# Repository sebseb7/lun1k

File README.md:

lun1k
=====

find a toolchain here: https://launchpad.net/gcc-arm-embedded

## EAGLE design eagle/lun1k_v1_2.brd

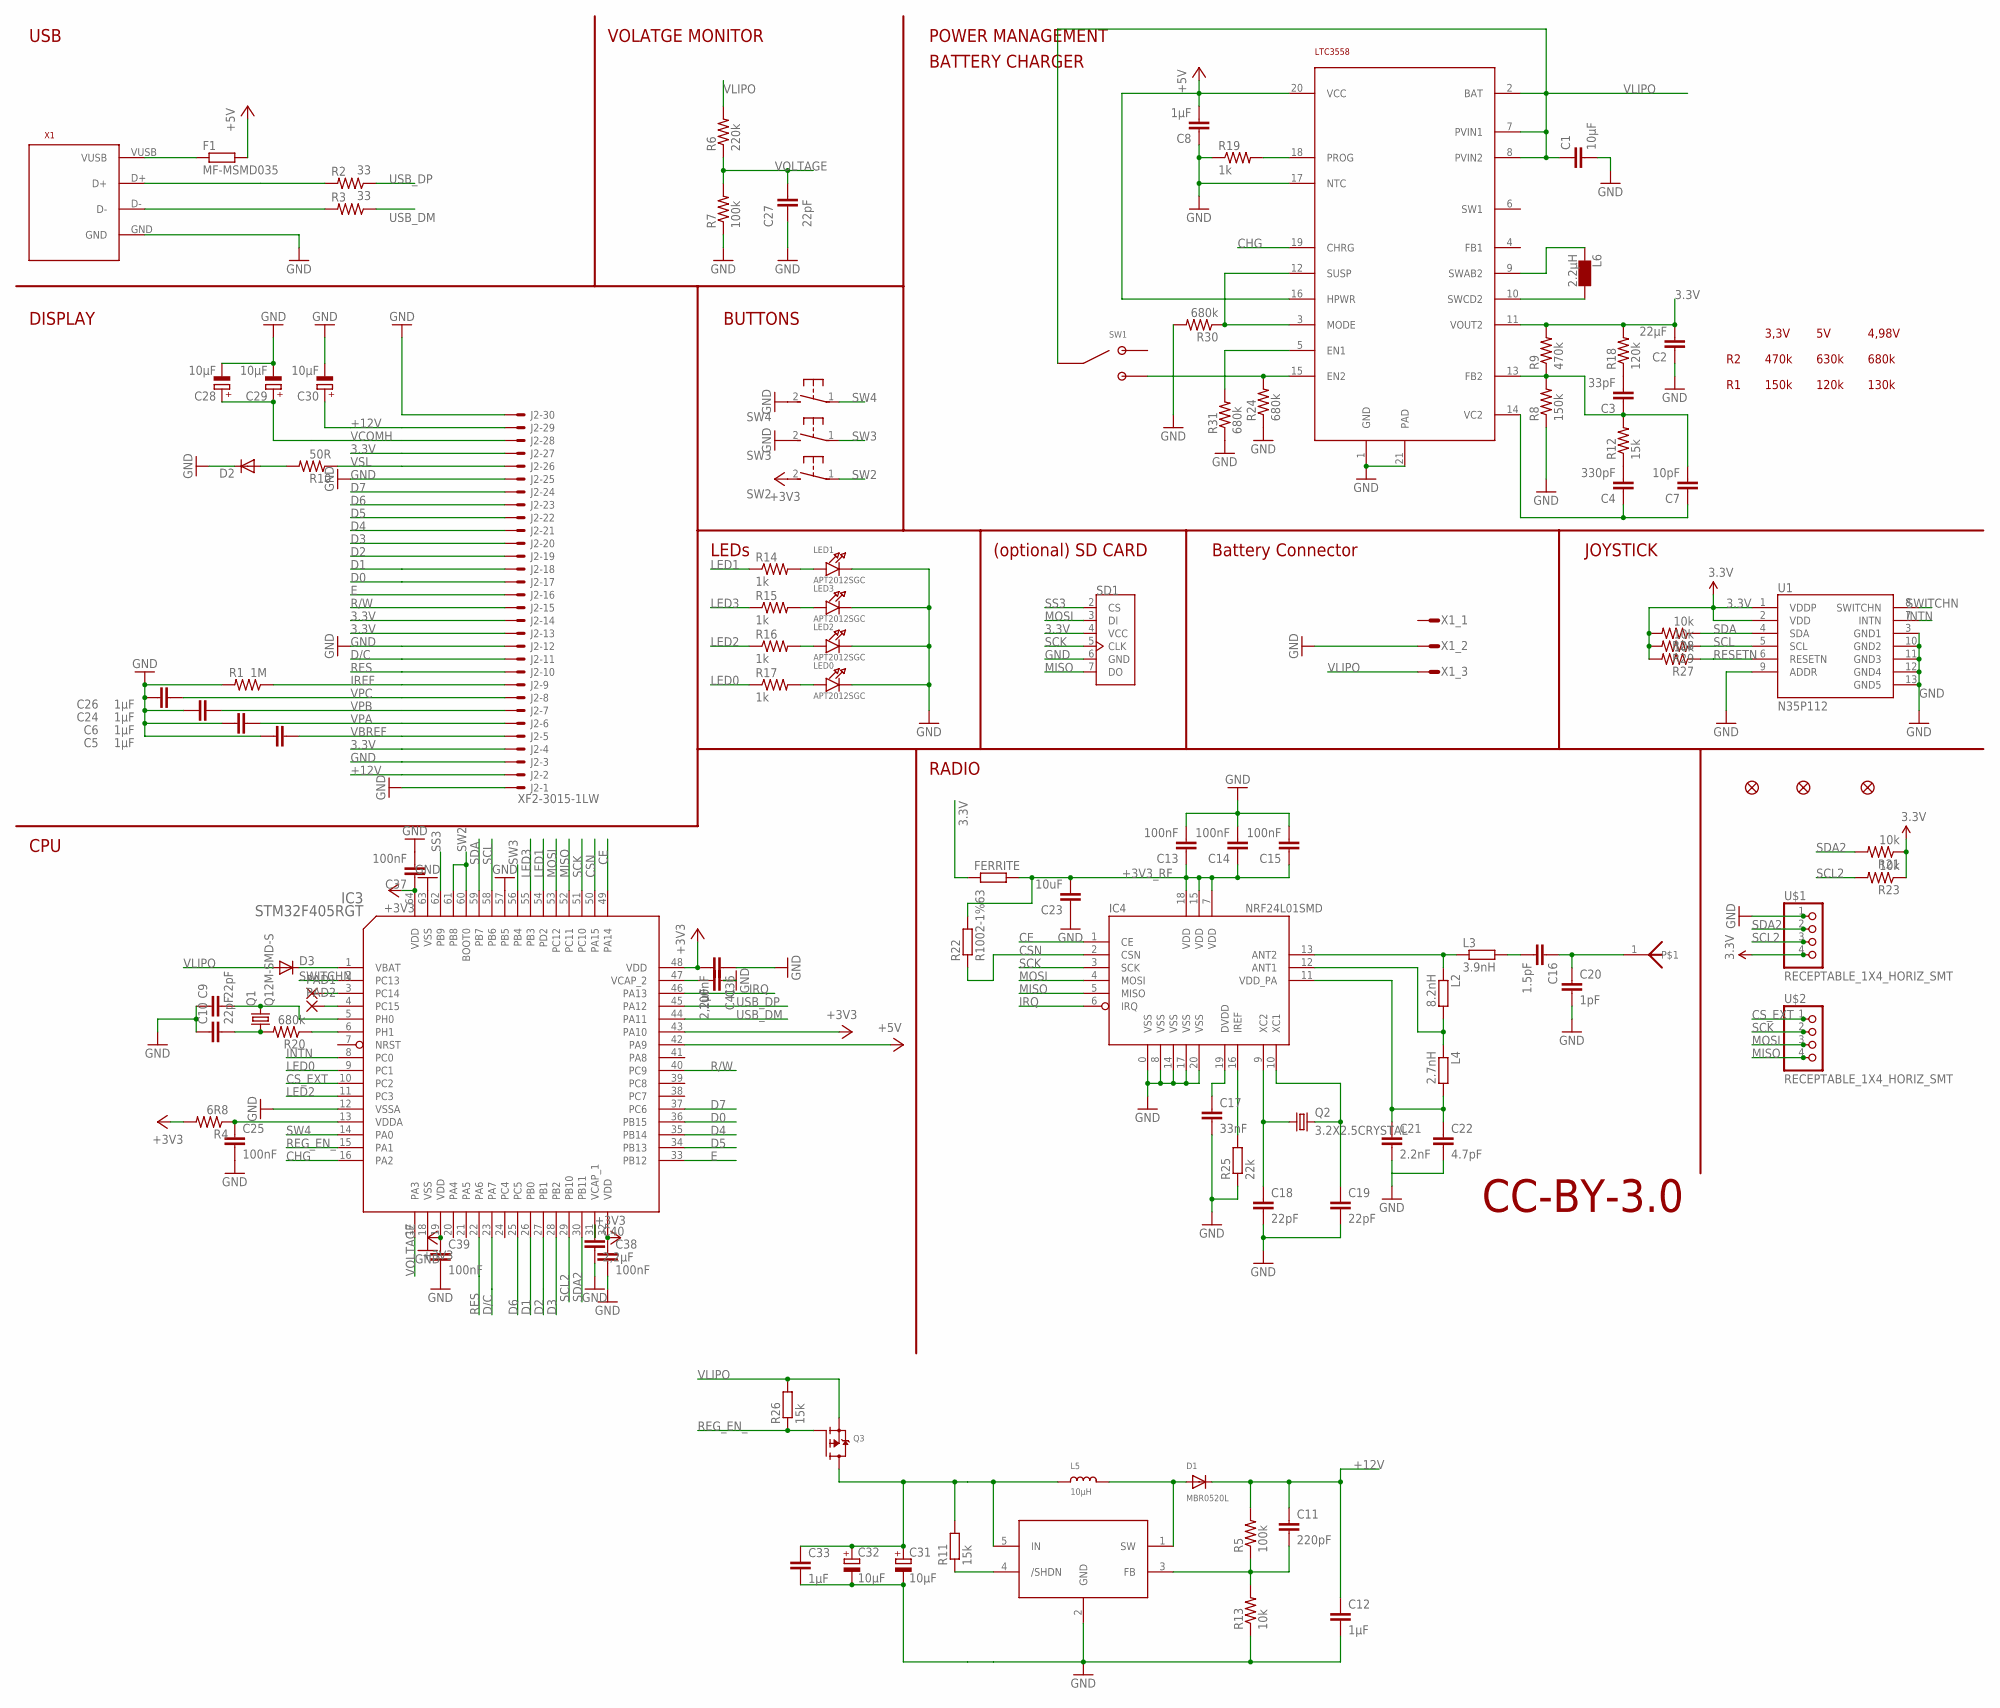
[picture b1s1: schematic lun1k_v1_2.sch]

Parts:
ANT: CHIPANTENNA
C1: 10µF; 0805
C2: 22µF; 0805
C3: 33pF; 0805
C4: 330pF; 0805
C5, C6, C8, C12, C24, C26, C33: 1µF; 0805
C7: 10pF; 0805
C9, C10, C27: 22pF; 0402-CAP
C11: 220pF; 0805
C13, C14, C15: 100nF; C0402K
C16: 1.5pF; C0402K
C17: 33nF; C0402K
C18, C19: 22pF; C0402K
C20: 1pF; C0402K
C21: 2.2nF; C0402K
C22: 4.7pF; C0402K
C23: 10uF; C0805K
C25, C36, C37, C38, C39: 100nF; 0402-CAP
C28, C29, C30, C31, C32: 10µF; SMC_A
C40, C41: 2,2µF; 0805
D1: MBR0520L; SOD-123
D2, D3: DIODE-SOD323-R; SOD323-R
F1: MF-MSMD035; R1210
FERRITE: R-EU_R0805; R0805
FID1, FID2, FID3: FIDUCIAL1.5X3; FIDUCIAL-1.5X3
IC1: LTC3558; UD-QFN20
IC2: LM27313; SOT23-5L
IC3: STM32F405RGT; LQFP64
IC4: NRF24L01SMD; QFN20
J2: XF2-3015-1LW; XF2H-3015-1LW
L2: 8.2nH; R0402
L3: 3.9nH; R0402
L4: 2.7nH; R0402
L5: 10µH; INDUCTOR_1007
L6: 2.2µH; CDRH3D16
LED0, LED1, LED2, LED3: APT2012SGC; CHIPLED_0805
PAD1, PAD2: SMD2; SMD1,27-2,54
Q1: Q12M-SMD-S; X22
Q2: 3.2X2.5CRYSTAL; CRYSTAL3.2X2.5
Q3: MOSFET-P; SOT23-R
R1: 1M; 0805
R2, R3: 33; 0402-RES
R4: 6R8; 0402-RES
R5: 100k; 0805
R6: 220k; 0402-RES
R7: 100k; 0402-RES
R8: 150k; 0805
R9: 470k; 0805
R10: 50R; 0805
R11, R26: 15k; R0402
R12: 15k; 0805
R13: 10k; 0805
R14, R15, R16, R17: 1k; 0402-RES
R18: 120k; 0805
R19: 1k; 0805
R20, R24, R30, R31: 680k; 0402-RES
R21, R23, R27, R28, R29: 10k; 0402-RES
R22: R1002-1%63; R0603
R25: 22k; R0603
SD1: MICROSD_SF-MICROSD; MICROSD_MICROSD
SW1: JS102011SAQN
SW2, SW3, SW4: SWITCH_MCTAEF
U1: N35P112
U$1, U$2: RECEPTABLE_1X4_HORIZ_SMT
X1: MICROUSB; MICROAB
X1_: JST-PH3

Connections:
3.3V: C2.2, C36.2, C37.1, C38.1, C39.1, FERRITE.1, IC1.11 (VOUT2), IC3.19 (VDD), IC3.32 (VDD), IC3.43 (PA10), IC3.48 (VDD), IC3.64 (VDD), J2.4 (MS), J2.13 (MS), J2.14 (MS), J2.27 (MS), R4.2, R9.2, R18.2, R21.1, R23.1, R27.2, R28.2, R29.2, SD1.4 (VCC), SW2.2, U1.1 (VDDP), U1.2 (VDD), U$1.4, U$1.4@1 (4)
+3V3_RF: C13.1, C14.1, C15.1, C23.2, FERRITE.2, IC4.7 (VDD), IC4.15 (VDD), IC4.18 (VDD), R22.2
+5V: C8.2, F1.2, IC1.16 (HPWR), IC1.20 (VCC), IC3.42 (PA9)
+12V: C11.1, C12.1, C30.+, D1.C, J2.2 (MS), J2.29 (MS), R5.2
CE: IC3.49 (PA14), IC4.1 (CE)
CHG: IC1.19 (CHRG), IC3.16 (PA2)
CSN: IC3.50 (PA15), IC4.2 (CSN), R22.1
CS_EXT: IC3.10 (PC2), U$2.1, U$2.1@1 (1)
D0: IC3.36 (PB15), J2.17 (MS)
D1: IC3.26 (PB0), J2.18 (MS)
D2: IC3.27 (PB1), J2.19 (MS)
D3: IC3.28 (PB2), J2.20 (MS)
D4: IC3.35 (PB14), J2.21 (MS)
D5: IC3.34 (PB13), J2.22 (MS)
D6: IC3.25 (PC5), J2.23 (MS)
D7: IC3.37 (PC6), J2.24 (MS)
D+: R2.2, X1.D+
D-: R3.2, X1.D-
D/C: IC3.23 (PA7), J2.11 (MS)
E: IC3.33 (PB12), J2.16 (MS)
EN2: IC1.15 (EN2), R24.2, SW1.3
GND: C1.2, C2.1, C5.1, C6.1, C8.1, C9.1, C10.1, C12.2, C13.2, C14.2, C15.2, C17.2, C18.2, C19.2, C20.2, C21.2, C22.2, C23.1, C24.1, C25.2, C26.1, C27.1, C28.-, C29.-, C30.-, C31.-, C32.-, C33.2, C36.1, C37.2, C38.2, C39.2, C40.2, C41.1, D2.C, IC1.1 (GND), IC1.17 (NTC), IC1.21 (PAD), IC2.2 (GND), IC3.12 (VSSA), IC3.18 (VSS), IC3.57 (PB5), IC3.63 (VSS), IC4.0 (VSS), IC4.8 (VSS), IC4.14 (VSS), IC4.17 (VSS), IC4.20 (VSS), J2.1 (MSV), J2.3 (MS), J2.12 (MS), J2.25 (MS), J2.30 (MS), LED0.C, LED1.C, LED2.C, LED3.C, R1.2, R7.1, R8.1, R13.1, R19.1, R24.1, R25.1, R30.2, R31.1, SD1.6 (GND), SW3.2, SW4.2, U1.3 (GND1), U1.9 (ADDR), U1.10 (GND2), U1.11 (GND3), U1.12 (GND4), U1.13 (GND5), U$1.1, U$1.1@1 (1), X1.GND, X1_.2
INTN: IC3.8 (PC0), U1.7 (INTN)
IREF: J2.9 (MS), R1.1
IRQ: IC3.46 (PA13), IC4.6 (IRQ)
LED0: IC3.9 (PC1), R17.1
LED1: IC3.54 (PD2), R14.1
LED2: IC3.11 (PC3), R16.1
LED3: IC3.55 (PB3), R15.1
MISO: IC3.52 (PC11), IC4.5 (MISO), SD1.7 (DO), U$2.4, U$2.4@1 (4)
MOSI: IC3.53 (PC12), IC4.4 (MOSI), SD1.3 (DI), U$2.3, U$2.3@1 (3)
unnamed: C9.2, IC3.5 (PH0), Q1.3 (2)
unnamed: IC1.18 (PROG), R19.2
unnamed: C10.2, Q1.1, R20.2
unnamed: LED0.A, R17.2
unnamed: LED2.A, R16.2
unnamed: LED3.A, R15.2
unnamed: C3.1, C7.2, IC1.13 (FB2), R8.2, R9.1, R12.2
unnamed: F1.1, X1.VUSB
unnamed: LED1.A, R14.2
unnamed: C18.1, IC4.9 (XC2), Q2.1
unnamed: C19.1, IC4.10 (XC1), Q2.3 (2)
unnamed: ANT.1, C16.1, C20.1
unnamed: C3.2, R18.1
unnamed: D2.A, R10.2
unnamed: C25.1, IC3.13 (VDDA), R4.1
unnamed: C4.2, R12.1
unnamed: C4.1, C7.1, IC1.14 (VC2)
unnamed: IC1.10 (SWCD2), L6.P$1 (1)
unnamed: C40.1, IC3.31 (VCAP_1)
unnamed: C41.2, IC3.47 (VCAP_2)
unnamed: IC3.3 (PC14), PAD1.1
unnamed: IC1.9 (SWAB2), L6.P$2 (2)
unnamed: IC3.4 (PC15), PAD2.1
unnamed: D1.A, IC2.1 (SW), L5.P$2 (2)
unnamed: IC1.3 (MODE), IC1.12 (SUSP), R30.1
unnamed: C11.2, IC2.3 (FB), R5.1, R13.2
unnamed: IC1.5 (EN1), R31.2
unnamed: IC3.6 (PH1), R20.1
unnamed: D3.C, IC3.1 (VBAT)
unnamed: IC2.4 (/SHDN), R11.1
unnamed: C17.1, IC4.19 (DVDD)
unnamed: IC4.16 (IREF), R25.2
unnamed: C21.1, C22.1, IC4.11 (VDD_PA), L4.2
unnamed: IC4.12 (ANT1), L2.2, L4.1
unnamed: IC4.13 (ANT2), L2.1, L3.1
unnamed: C16.2, L3.2
R/W: IC3.40 (PC9), J2.15 (MS)
REG_EN_: IC3.15 (PA1), Q3.1 (G), R26.1
RES: IC3.22 (PA6), J2.10 (MS)
RESETN: R27.1, U1.6 (RESETN)
SCK: IC3.51 (PC10), IC4.3 (SCK), SD1.5 (CLK), U$2.2, U$2.2@1 (2)
SCL: IC3.58 (PB6), R29.1, U1.5 (SCL)
SCL2: IC3.29 (PB10), R23.2, U$1.3, U$1.3@1 (3)
SDA: IC3.59 (PB7), R28.1, U1.4 (SDA)
SDA2: IC3.30 (PB11), R21.2, U$1.2, U$1.2@1 (2)
SS3: IC3.62 (PB9), SD1.2 (CS)
SW2: IC3.60 (BOOT0), IC3.61 (PB8), SW2.1
SW3: IC3.56 (PB4), SW3.1
SW4: IC3.14 (PA0), SW4.1
SWITCHN: IC3.2 (PC13), U1.8 (SWITCHN)
USB_DM: IC3.44 (PA11), R3.1
USB_DP: IC3.45 (PA12), R2.1
VBREF: C5.2, J2.5 (MS)
VCOMH: C28.+, C29.+, J2.28 (MS)
VLIPO: C1.1, D3.A, IC1.2 (BAT), IC1.7 (PVIN1), IC1.8 (PVIN2), Q3.2 (S), R6.2, R26.2, SW1.2, X1_.3
VOLTAGE: C27.2, IC3.17 (PA3), R6.1, R7.2
VPA: C6.2, J2.6 (MS)
VPB: C24.2, J2.7 (MS)
VPC: C26.2, J2.8 (MS)
VREGIN: C31.+, C32.+, C33.1, IC2.5 (IN), L5.P$1 (1), Q3.3 (D), R11.2
VSL: J2.26 (MS), R10.1

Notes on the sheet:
POWER MANAGEMENT
DISPLAY
USB
BATTERY CHARGER
VOLATGE MONITOR
LEDs
(optional) SD CARD
JOYSTICK
CPU
RADIO
CC-BY-3.0
BUTTONS
3,3V
4,98V
470k
150k
630k
120k
680k
130k
Battery Connector

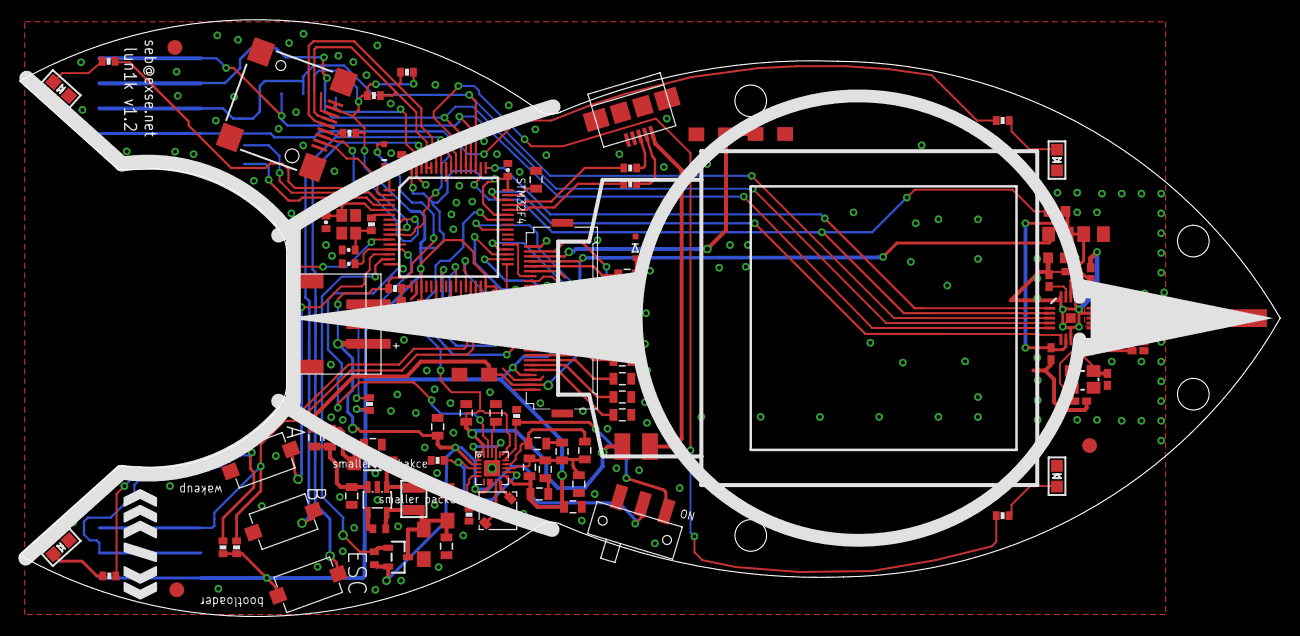
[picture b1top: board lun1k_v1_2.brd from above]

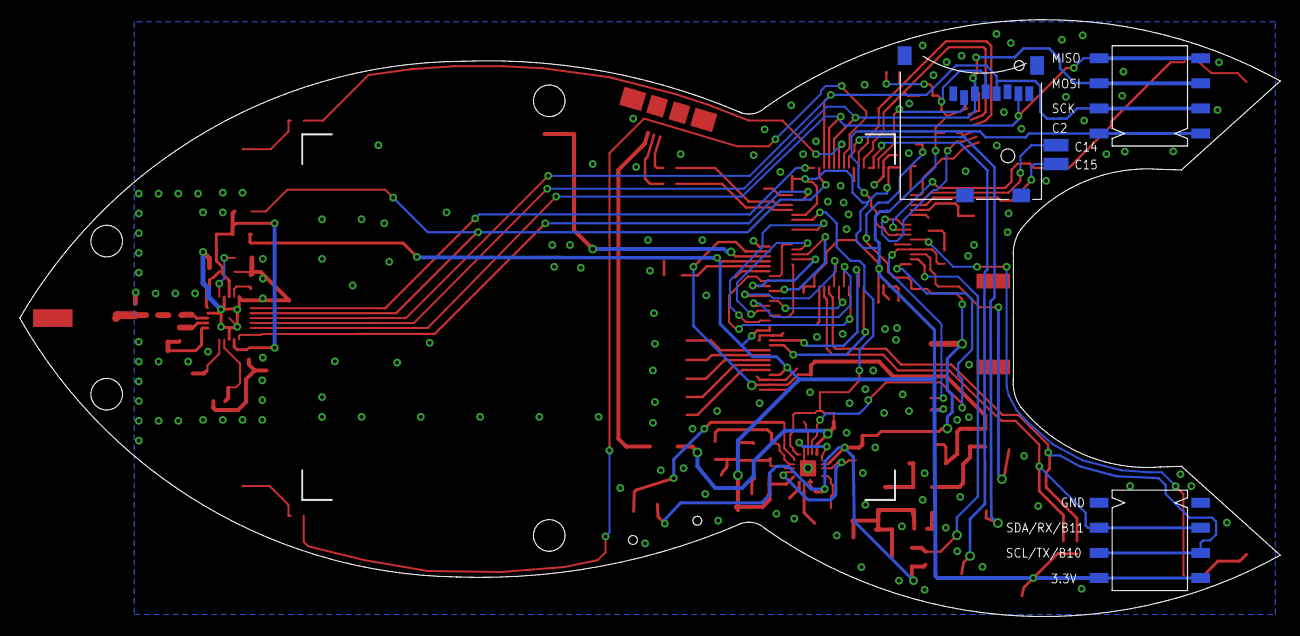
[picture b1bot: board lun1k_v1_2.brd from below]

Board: 2 copper layers, 127.6 x 60.4 mm, 108 parts (5 on the bottom side), 92 nets.

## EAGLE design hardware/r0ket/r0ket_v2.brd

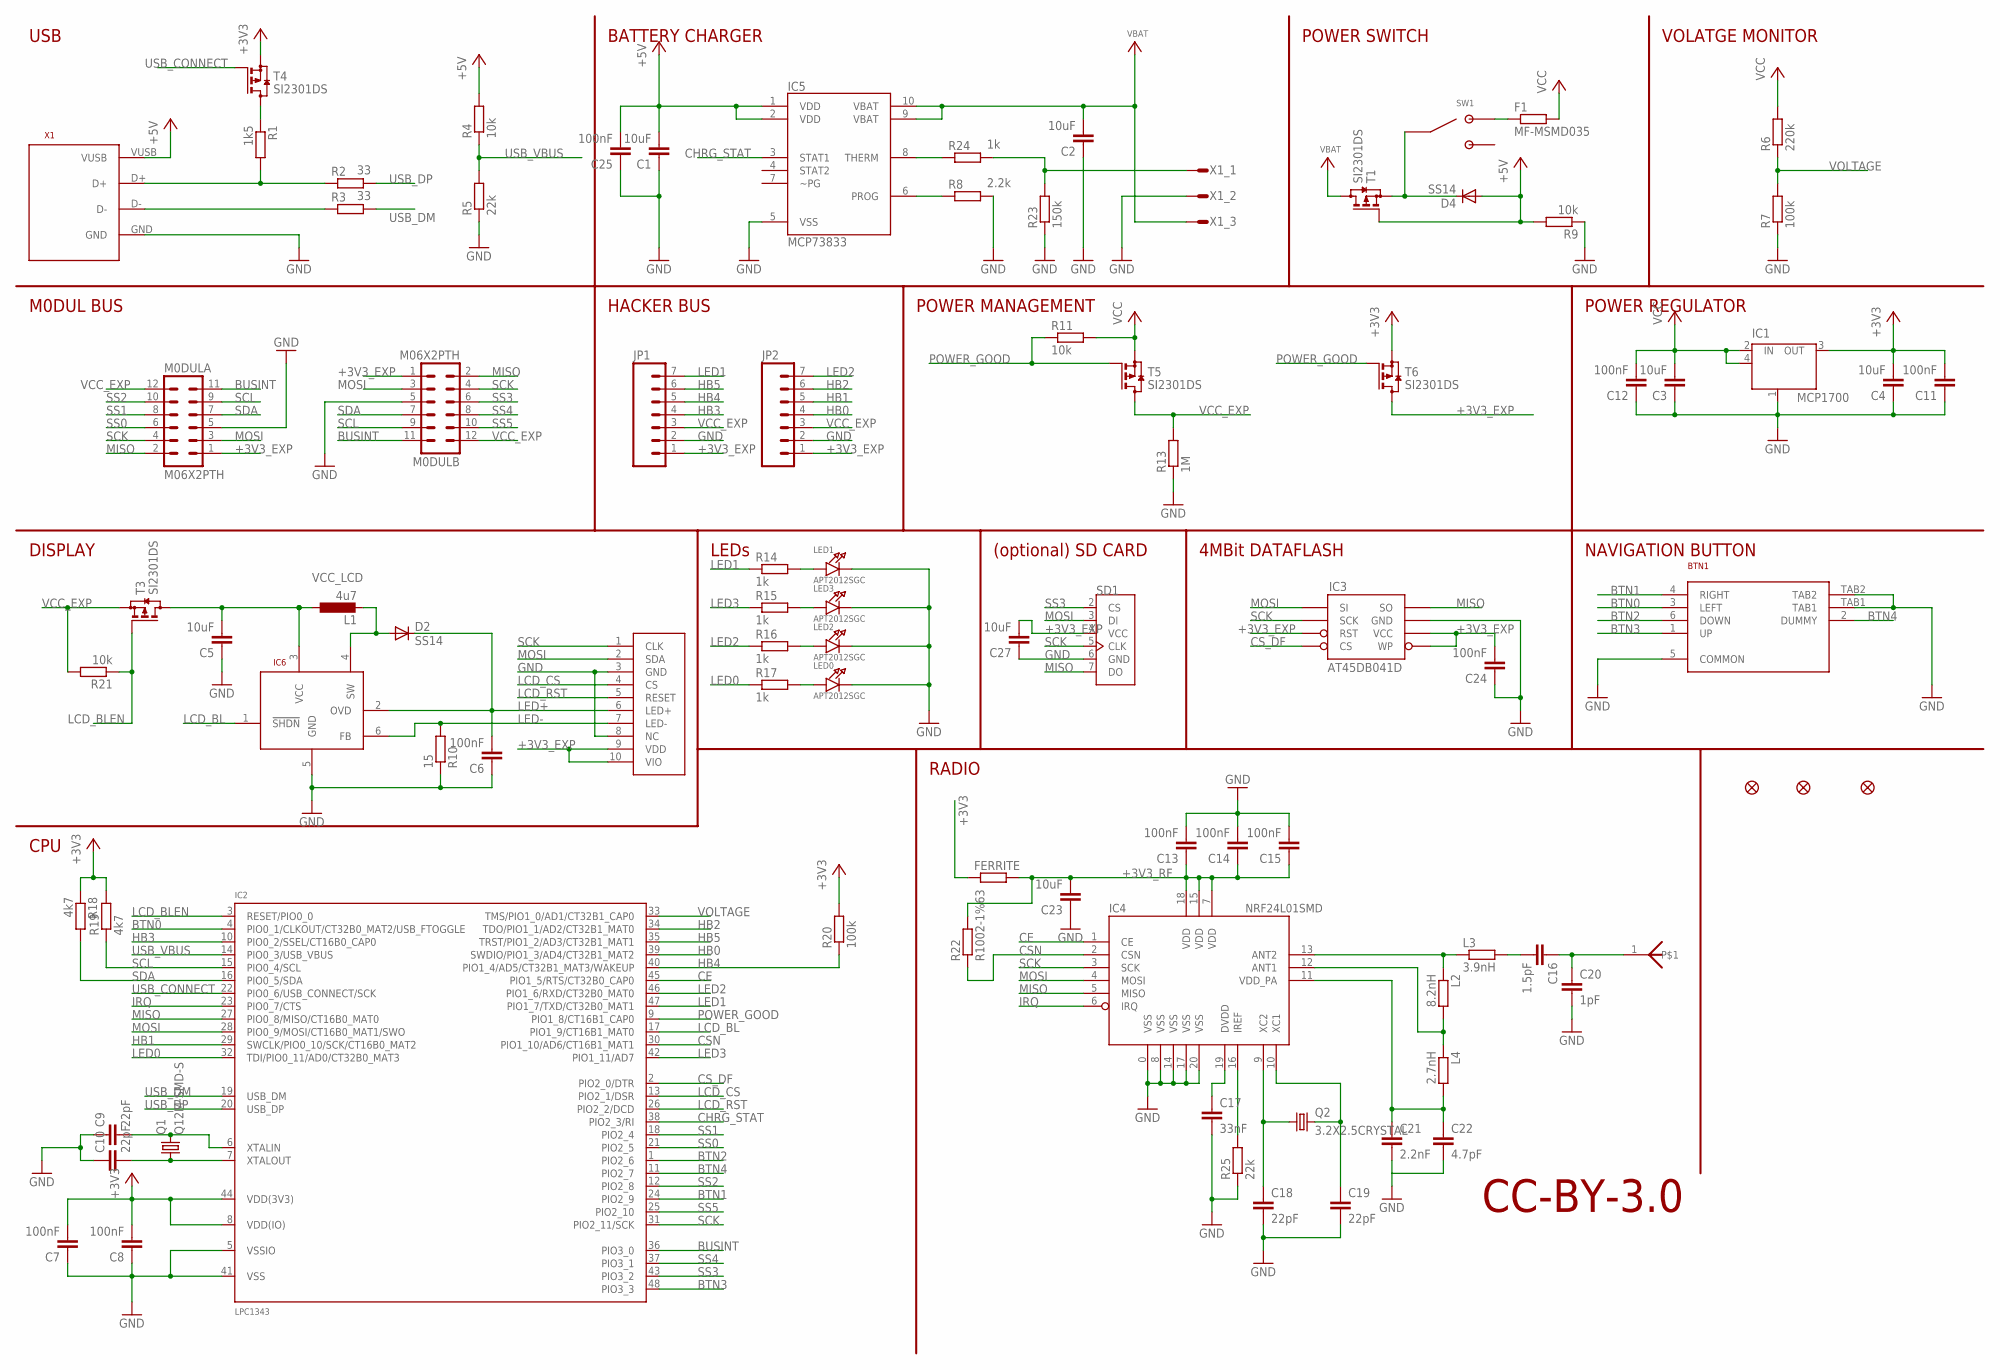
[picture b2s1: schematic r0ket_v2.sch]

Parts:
ANT: CHIPANTENNA
BTN1: MCMT5-F-V
C1, C2, C3, C4, C5, C23, C27: 10uF; C0805K
C6, C7, C8, C11, C12, C13, C14, C15, C24, C25: 100nF; C0402K
C9, C10, C18, C19: 22pF; C0402K
C16: 1.5pF; C0402K
C17: 33nF; C0402K
C20: 1pF; C0402K
C21: 2.2nF; C0402K
C22: 4.7pF; C0402K
D2, D4: SS14; SMB
F1: MF-MSMD035; R1210
FERRITE: R-EU_R0805; R0805
FID1, FID2, FID3: FIDUCIAL1.5X3; FIDUCIAL-1.5X3
IC1: MCP1700; SOT89
IC2: LPC1343; LQFP48
IC3: AT45DB041D; SO08
IC4: NRF24L01SMD; QFN20
IC5: MCP73833; MSOP-10
IC6: TB62737; SUPERSOT6
JP1, JP2: M07; 1X07
L1: 4u7; 0806
L2: 8.2nH; R0402
L3: 3.9nH; R0402
L4: 2.7nH; R0402
LED0, LED1, LED2, LED3: APT2012SGC; CHIPLED_0805
M0DULA, M0DULB: M06X2PTH; MA06-2
Q1: Q12M-SMD-S; CTS406
Q2: 3.2X2.5CRYSTAL; CRYSTAL3.2X2.5
R1: 1k5; R0603
R2, R3: 33; R0603
R4, R9, R11, R21: 10k; R0603
R5, R25: 22k; R0603
R6: 220k; R0603
R7, R20: 100k; R0603
R8: 2.2k; R0603
R10: 15; R0603
R13: 1M; R0603
R14, R15, R16, R17, R24: 1k; R0603
R18, R19: 4k7; R0603
R22: R1002-1%63; R0603
R23: 150k; R0603
SD1: MICROSD_SF-MICROSD; MICROSD_MICROSD
SW1: JS102011SAQN
T1, T3, T4, T5, T6: SI2301DS; SOT23
X1: MICROUSB; MICROAB
X1_: JST-PH3
X2: NOKIA; DF23

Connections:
+3V3: C4.2, C7.2, C8.2, C11.2, FERRITE.1, IC1.3 (OUT), IC2.8 (VDD(IO)), IC2.44 (VDD(3V3)), R18.1, R19.2, R20.2, T4.2 (S), T6.2 (S)
+3V3_EXP: C24.2, C27.2, IC3.3 (RST), IC3.5 (WP), IC3.6 (VCC), JP1.1, JP2.1, M0DULA.1, M0DULB.1, SD1.4 (VCC), T6.3 (D), X2.9 (VDD), X2.10 (VIO)
+3V3_RF: C13.1, C14.1, C15.1, C23.2, FERRITE.2, IC4.7 (VDD), IC4.15 (VDD), IC4.18 (VDD), R22.2
+5V: C1.2, C25.2, D4.A, IC5.1 (VDD), IC5.2 (VDD), R4.2, R9.2, T1.1 (G), X1.VUSB
BTN0: BTN1.3 (LEFT), IC2.4 (PIO0_1/CLKOUT/CT32B0_MAT2/USB_FTOGGLE)
BTN1: BTN1.4 (RIGHT), IC2.24 (PIO2_9)
BTN2: BTN1.6 (DOWN), IC2.1 (PIO2_6)
BTN3: BTN1.1 (UP), IC2.48 (PIO3_3)
BTN4: BTN1.2 (DUMMY), IC2.11 (PIO2_7)
BUSINT: IC2.36 (PIO3_0), M0DULA.11, M0DULB.11
CE: IC2.45 (PIO1_5/RTS/CT32B0_CAP0), IC4.1 (CE)
CHRG_STAT: IC2.38 (PIO2_3/RI), IC5.3 (STAT1)
CSN: IC2.30 (PIO1_10/AD6/CT16B1_MAT1), IC4.2 (CSN), R22.1
CS_DF: IC2.2 (PIO2_0/DTR), IC3.4 (CS)
D+: R1.2, R2.2, X1.D+
D-: R3.2, X1.D-
GND: BTN1.5 (COMMON), BTN1.TAB1, BTN1.TAB2, C1.1, C2.1, C3.1, C4.1, C5.1, C6.1, C7.1, C8.1, C9.1, C10.1, C11.1, C12.1, C13.2, C14.2, C15.2, C17.2, C18.2, C19.2, C20.2, C21.2, C22.2, C23.1, C24.1, C25.1, C27.1, IC1.1 (GND/ADJ), IC2.5 (VSSIO), IC2.41 (VSS), IC3.7 (GND), IC4.0 (VSS), IC4.8 (VSS), IC4.14 (VSS), IC4.17 (VSS), IC4.20 (VSS), IC5.5 (VSS), IC6.5 (GND), JP1.2, JP2.2, LED0.C, LED1.C, LED2.C, LED3.C, M0DULA.5, M0DULB.5, R5.1, R7.1, R8.1, R9.1, R10.1, R13.1, R23.1, R25.1, SD1.6 (GND), X1.GND, X1_.2, X2.3 (GND), X2.8 (NC)
HB0: IC2.39 (SWDIO/PIO1_3/AD4/CT32B1_MAT2), JP2.4
HB1: IC2.29 (SWCLK/PIO0_10/SCK/CT16B0_MAT2), JP2.5
HB2: IC2.34 (TDO/PIO1_1/AD2/CT32B1_MAT0), JP2.6
HB3: IC2.10 (PIO0_2/SSEL/CT16B0_CAP0), JP1.4
HB4: IC2.40 (PIO1_4/AD5/CT32B1_MAT3/WAKEUP), JP1.5, R20.1
HB5: IC2.35 (TRST/PIO1_2/AD3/CT32B1_MAT1), JP1.6
IRQ: IC2.23 (PIO0_7/CTS), IC4.6 (IRQ)
LCD_BL: IC2.17 (PIO1_9/CT16B1_MAT0), IC6.1 (!SHDN)
LCD_BLEN: IC2.3 (RESET/PIO0_0), R21.1, T3.1 (G)
LCD_CS: IC2.13 (PIO2_1/DSR), X2.4 (CS)
LCD_RST: IC2.26 (PIO2_2/DCD), X2.5 (RESET)
LED0: IC2.32 (TDI/PIO0_11/AD0/CT32B0_MAT3), R17.1
LED1: IC2.47 (PIO1_7/TXD/CT32B0_MAT1), JP1.7, R14.1
LED2: IC2.46 (PIO1_6/RXD/CT32B0_MAT0), JP2.7, R16.1
LED3: IC2.42 (PIO1_11/AD7), R15.1
LED+: C6.2, D2.C, IC6.2 (OVD), X2.6 (LED+)
LED-: IC6.6 (FB), R10.2, X2.7 (LED-)
MISO: IC2.27 (PIO0_8/MISO/CT16B0_MAT0), IC3.8 (SO), IC4.5 (MISO), M0DULA.2, M0DULB.2, SD1.7 (DO)
MOSI: IC2.28 (PIO0_9/MOSI/CT16B0_MAT1/SWO), IC3.1 (SI), IC4.4 (MOSI), M0DULA.3, M0DULB.3, SD1.3 (DI), X2.2 (SDA)
unnamed: C9.2, IC2.6 (XTALIN), Q1.3 (2)
unnamed: IC5.8 (THERM), R24.2
unnamed: C10.2, IC2.7 (XTALOUT), Q1.1
unnamed: LED0.A, R17.2
unnamed: LED2.A, R16.2
unnamed: LED3.A, R15.2
unnamed: R23.2, R24.1, X1_.1
unnamed: D4.C, SW1.2, T1.2 (S)
unnamed: LED1.A, R14.2
unnamed: C18.1, IC4.9 (XC2), Q2.1
unnamed: C19.1, IC4.10 (XC1), Q2.3 (2)
unnamed: ANT.1, C16.1, C20.1
unnamed: IC5.6 (PROG), R8.2
unnamed: D2.A, IC6.4 (SW), L1.2
unnamed: F1.1, SW1.1
unnamed: R1.1, T4.3 (D)
unnamed: C17.1, IC4.19 (DVDD)
unnamed: IC4.16 (IREF), R25.2
unnamed: C21.1, C22.1, IC4.11 (VDD_PA), L4.2
unnamed: IC4.12 (ANT1), L2.2, L4.1
unnamed: IC4.13 (ANT2), L2.1, L3.1
unnamed: C16.2, L3.2
POWER_GOOD: IC2.9 (PIO1_8/CT16B1_CAP0), R11.1, T5.1 (G), T6.1 (G)
SCK: IC2.31 (PIO2_11/SCK), IC3.2 (SCK), IC4.3 (SCK), M0DULA.4, M0DULB.4, SD1.5 (CLK), X2.1 (CLK)
SCL: IC2.15 (PIO0_4/SCL), M0DULA.9, M0DULB.9, R19.1
SDA: IC2.16 (PIO0_5/SDA), M0DULA.7, M0DULB.7, R18.2
SS0: IC2.21 (PIO2_5), M0DULA.6
SS1: IC2.18 (PIO2_4), M0DULA.8
SS2: IC2.12 (PIO2_8), M0DULA.10
SS3: IC2.43 (PIO3_2), M0DULB.6, SD1.2 (CS)
SS4: IC2.37 (PIO3_1), M0DULB.8
SS5: IC2.25 (PIO2_10), M0DULB.10
USB_CONNECT: IC2.22 (PIO0_6/USB_CONNECT/SCK), T4.1 (G)
USB_DM: IC2.19 (USB_DM), R3.1
USB_DP: IC2.20 (USB_DP), R2.1
USB_VBUS: IC2.14 (PIO0_3/USB_VBUS), R4.1, R5.2
VBAT: C2.2, IC5.9 (VBAT), IC5.10 (VBAT), T1.3 (D), X1_.3
VCC: C3.2, C12.2, F1.2, IC1.2 (IN), IC1.4 (IN), R6.2, R11.2, T5.2 (S)
VCC_EXP: JP1.3, JP2.3, M0DULA.12, M0DULB.12, R13.2, R21.2, T3.2 (S), T5.3 (D)
VCC_LCD: C5.2, IC6.3 (VCC), L1.1, T3.3 (D)
VOLTAGE: IC2.33 (TMS/PIO1_0/AD1/CT32B1_CAP0), R6.1, R7.2

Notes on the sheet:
M0DUL BUS
HACKER BUS
POWER MANAGEMENT
POWER REGULATOR
DISPLAY
USB
BATTERY CHARGER
POWER SWITCH
VOLATGE MONITOR
LEDs
(optional) SD CARD
4MBit DATAFLASH
NAVIGATION BUTTON
CPU
RADIO
CC-BY-3.0

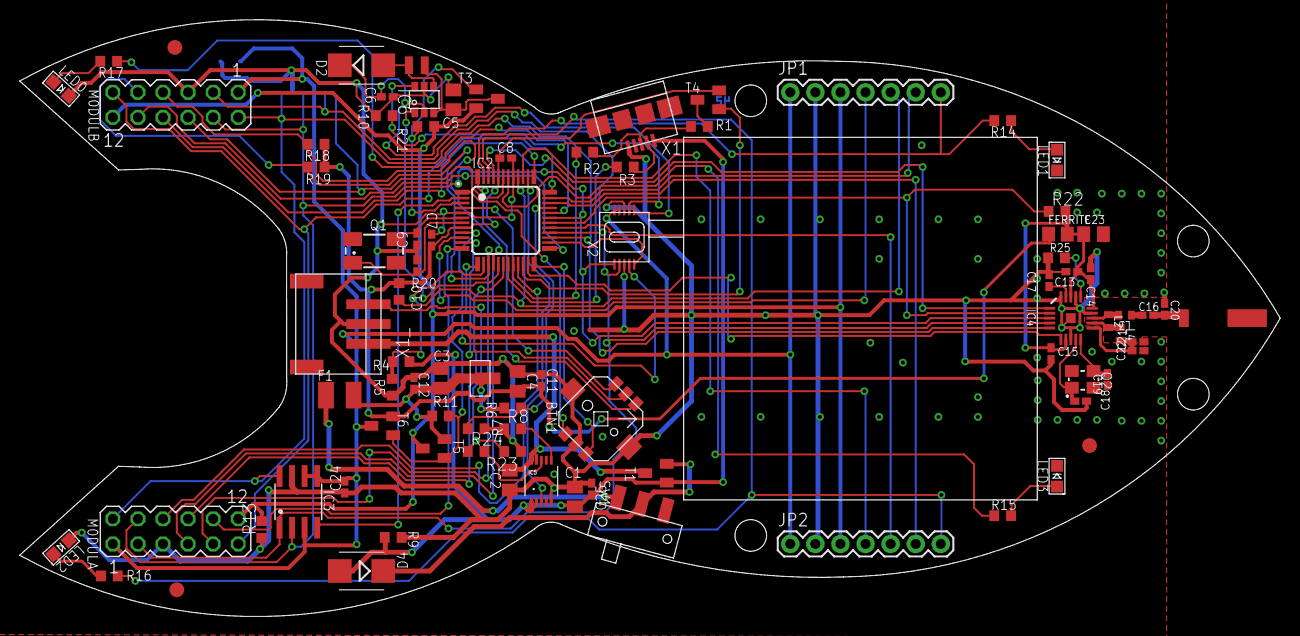
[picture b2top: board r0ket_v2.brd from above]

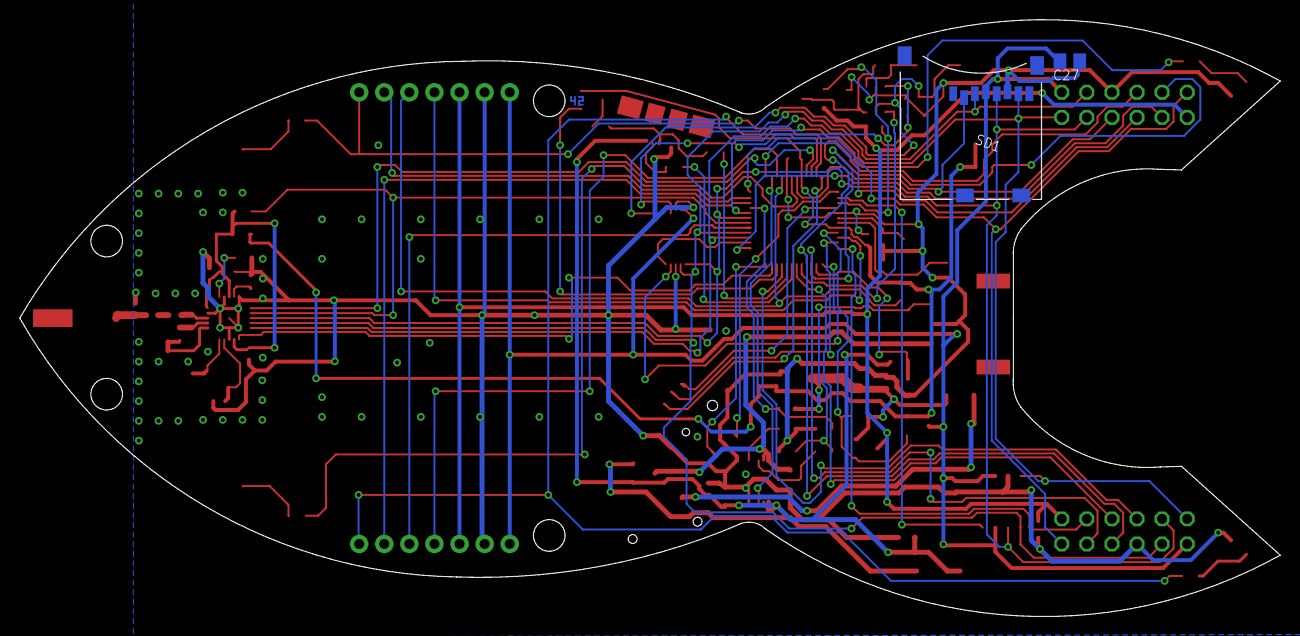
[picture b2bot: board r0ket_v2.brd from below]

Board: 2 copper layers, 127.6 x 60.4 mm, 89 parts (2 on the bottom side), 77 nets.

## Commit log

2012-09-26 removed everything except r0ket_v2.sch r0ket_v2.brd and badge.lbr
2012-09-26 converted all eagle files to v6
2012-09-26 removed a lot of components
2012-09-26 renamed eagle files
2012-09-27 added oled and 12v regulator
2012-09-27 added farnell number for pfc connector
2012-09-27 some wire cleanup
2012-09-27 added cpu
2012-09-27 fixed oled placement
2012-09-27 placed components for the oled
2012-09-27 placed mcu
2012-09-27 replaced 0402 packages
2012-09-27 smaller crystal
2012-09-27 routing
2012-09-27 placed analog joystick
2012-09-27 placed buttons
2012-09-27 completely removed old supply & management
2012-09-27 some resistors: 0603 -> 0402
2012-09-27 new lipo charger
2012-09-27 button text
2012-09-27 routeing
2012-09-27 current progress of the routing
2012-09-27 module connector
2012-10-01 labeling
2012-10-01 milestone 1
2012-10-01 initial sumulator
2012-10-01 api change
2012-10-01 added 8x6 font
2012-10-01 switch 12V supply part 1
2012-10-01 switch 12V supply part 2
2012-10-01 font-template
2012-10-01 regulator final
2012-10-01 second ani
2012-10-03 updated images
2012-10-04 new variable-width 21pt font added
2012-10-04 small fixes
2012-10-04 remove old font and new lunik image
2012-10-05 unfinifhsed drivers
2012-11-01 minor changes
2012-11-02 post production fixes
2012-11-02 merge
2012-11-07 sim/Makefile: add Linux FLAGS for SDL
2012-11-07 tunnel animation
2012-11-07 animations/tunnel: bricked texture attempt
2012-11-07 cleanup, fixed some compiler warnings, lun1k <-> simulator compatibility
2012-11-07 fix for clang warning
2012-11-07 renamed attribute for constructor
2012-11-07 cleanup and directory reorganisation
2012-11-07 all globals should be static
2012-11-07 only 8k instead of 184k
2012-11-07 typo
2012-11-07 reorganize repo
2012-11-07 gitignore
2012-11-07 new animation
2012-11-07 font tools
2012-11-07 initial version of lun1k firmware
2012-11-07 printf now from libc
2012-11-08 limit fps to 30
2012-11-08 animations/tunnel: textured
2012-11-08 animations/tunnel_less_ram: texture & shading likewise
2012-11-08 animations/tunnel_less_ram: subsampling
2012-11-08 cleanup
2012-11-08 sim: smarter FRAMETIME
2012-11-08 sim: fix font path on linux
2012-11-08 animations/tunnel_less_ram: fiddle parameters
2012-11-08 animations/tunnel_less_ram: fix subsampling
2012-11-08 only 6 bit colors, like lun1k
2012-11-08 made a few things const
2012-11-08 slower is more realistic
2012-11-08 moved
2012-11-08 cleanup and cunstructor support for stm32f2
2012-11-08 readded asserts
2012-11-09 added fill_8x6
2012-11-09 simple tetris demo with 3 bots
2012-11-10 texture for todays party
2012-11-14 better gamma correction
2012-11-14 button support, smaller changes
2012-11-14 fixes
2012-11-14 color and button stub
2012-11-14 changed animationset
2012-11-14 no fsaa and no textture tunnel
2012-11-14 remoted 2nd texture
2012-11-14 removed F2 support
2012-11-14 added link to working stm32f4 toolchain
2012-11-14 fix math.c for simulator
2012-11-14 removed sdl_ttf dpendency
2012-11-14 animations: beginnings of a silly jumpnrun
2012-11-14 import fgl
    http://fgl.googlecode.com/svn/trunk/ at r17
2012-11-14 import libfixmath
    http://libfixmath.googlecode.com/svn/trunk/ at r84
2012-11-15 fgl_cube works in the sim
2012-11-15 fgl_cube: texture
2012-11-15 attempt to bring fgl to firmware
2012-11-16 tunnel
2012-11-17 debounce for all 4 buttons
2012-11-18 removed old tunnel
2012-11-18 removed 4xfsaa
2012-11-18 renamed tunnel_less_ram -> tunnel
2012-11-18 renamed tunnel_noaa -> tunnel_no_tex
2012-11-18 key support
2012-11-18 only stick key skips
2012-11-18 removed fgl (was included by accident)
2012-11-18 missing merge-fail bits
2012-11-18 readded jump
2012-11-20 animations/gap
2012-11-20 get_key_state()
2012-11-20 animations/linebox
2012-11-20 double -> float (to make use of the fpu, float is good enough)
2012-11-20 animations/{gap,jump}: static const textures
2012-11-20 _sinf() _cosf()
2012-11-20 beautified table and range check theta
2012-11-20 getSysTick()
2012-11-20 ported a voxel engine
    Source: https://github.com/trevornunes/voxel
2012-11-21 voxel: optimize, prettify, in firmware
2012-11-21 debug allocations
2012-11-21 newvox: optimize & prettify
2012-11-21 removed printf
2012-11-21 interference
2012-11-21 limit heap size
2012-11-21 init, deinit
2012-11-21 newvox.h
2012-11-21 out of memory
2012-11-21 fixed 2 warnings
2012-11-21 fixed warning
2012-11-21 fixed a few warnings, a few remain
2012-11-21 added colors
2012-11-21 chnaged the red channel
2012-11-21 red <-> blue
2012-11-21 removed warning
2012-11-21 who am I?
2012-11-21 mac stuff
2012-11-21 updated animation list
2012-12-04 sim/Makefile: echo -e
2012-12-04 fixes some warnings & malloc wrapper fix (still not working on linux)
2012-12-05 fix no non linux
2012-12-05 animations/notch works!
2012-12-05 animations/notch: fix rand() usage
2012-12-05 disabled malloc wrapping on linux
2012-12-05 animations/notch: reduce memory footprint
    should malloc(81920) now
2012-12-05 animations/notch: brighter colors
2012-12-05 animations/notch: use arm __VSQRTF
2012-12-05 animations/notch: interlacing
2012-12-05 animations/notch: don't use arm __VSQRTF
2012-12-05 firmware: build notch demo
2012-12-05 animations/notch: tune up to 11
2012-12-11 animations/{cube,notch_fp}: incomplete stuff; armmath cosi()
2012-12-13 animations/bzr
    allocs 196608 bytes
2012-12-13 animations/bzr: use half the memory with int16_t, buggy
2012-12-13 animations/notch: now rendered in CD™!
    CD: Crappy Definition
2012-12-13 looks better now
2012-12-13 more like the original
2012-12-13 bzr plasma
2012-12-13 make it more psychedelic
2012-12-15 animations/bzr2: micro-optimize wrap-around
2012-12-15 animations/{bzr,bzr2}: static globals
2012-12-15 animations/bzr2: draw frametime
2012-12-15 animations/bzr2: micro-optimize with __QADD16/__QSUB16
    accounts for <5% less frametime
2012-12-17 Revert "animations/bzr2: micro-optimize with __QADD16/__QSUB16"
    This reverts commit 4fa1ac7b4fa2a280ec46150d3a86e4e23880c761.
2012-12-18 animations/bzr2: rotozoom
2012-12-19 lun1k v11 prep
2012-12-19 removed dev board code
2012-12-19 removed dev-board code
2012-12-19 unoptimized lun1k v1.1 support completed
2012-12-19 finalized lin1k v11 optimization
2012-12-23 sim: rename fillRGB() to lcdFillRGB() like in firmware
2012-12-23 animations/fleatron
2012-12-24 animations/qr_clock, import generator code from https://github.com/zint/zint
2012-12-28 animations/qr_clock: cycle colors, quicker
2012-12-28 animations/bzr2: optimize scale sin()
2012-12-28 firmware/Makefile: build w/ zint, qr_code & fleatron by default
2012-12-29 animations/bzr2: calc every frame, show FPS instead of frametime
2012-12-29 animations/qr_clock: rm colors, change information
2012-12-29 sim/Makefile: build w/ zint too
2012-12-29 animations/29c3
2013-01-10 v1_2
2013-01-10 small fix
2013-01-10 reduced image size
2013-01-10 new sim image
2013-01-10 first bits from lun1k version 1.2
2013-01-10 script for generating portb map
2013-01-10 comment for v13
2013-01-17 fight warnings
2013-01-17 linux fix
2013-01-17 globals static !
2013-01-17 signedness
2013-01-17 sim build fix
2013-01-18 new fractal zoom animation
2013-01-18 beautifulisation of code
2013-01-19 calculating algo time
2013-01-19 now randomly choosing between 2 points and restart after maxzoom is archieved
2013-01-22 animations/kaleidoscope <faulty>
2013-01-29 hardware RNG interface
2013-01-31 device signature
2013-02-01 format
2013-02-03 bootloader rubustness
2013-02-10 fake movie player
2013-02-14 SD card & Fat32 support
2013-02-14 docs
2013-02-15 alignedment fix
2013-02-15 repo reorg
2013-02-15 eeprom emulatoin
2013-02-15 minor stuff
2013-02-15 groundwork for hal_file
2013-02-15 ignore simulator binaries
2013-02-15 fix last commit
2013-02-15 more apis
2013-02-15 updated flash layout
2013-02-15 added ability to prefill emulated eeprom
2013-02-15 split pages
2014-02-20 obsolete
2014-02-25 compiler warnings
2014-02-25 compiler waring
2014-07-28 joxstick driver
2014-07-28 gcc 4.9
2014-07-28 eeprom driver updates
2014-07-28 misc
2014-07-28 todo
2014-07-29 tetris updates
2014-07-29 save highscore to flash and preserver that flash area during firmware upgrade
2014-07-29 highscore fixes
2014-07-29 use hardware rng to seed pseudorng via srand
2014-07-29 flash_db & adc & pcb misc
2014-07-29 more animations
2014-07-30 v1.3 updates
2014-07-30 image updated
2014-07-30 moved stack and display_port_map to CCM RAM for performance
2014-07-30 compile syscalls
2014-07-30 joystick plasma disortion, fix simulator
2014-08-05 begin reorg for guilib
2014-08-06 color change
2014-08-06 test more elements
2014-10-09 build fix
2015-06-03 pacman
2015-06-04 more rules
2015-09-30 preliminary joystick support for pacman
2015-10-13 remove modulo bias
2015-12-02 fill2
2015-12-02 boudlerdash
2015-12-02 missing file
2015-12-02 bd fixes
2015-12-02 keywork
2015-12-06 bd updates

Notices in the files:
parts and their libraries:
SparkFun-Capacitors: Licensing: CC v3.0 Share-Alike You are welcome to use this library for commercial purposes.
